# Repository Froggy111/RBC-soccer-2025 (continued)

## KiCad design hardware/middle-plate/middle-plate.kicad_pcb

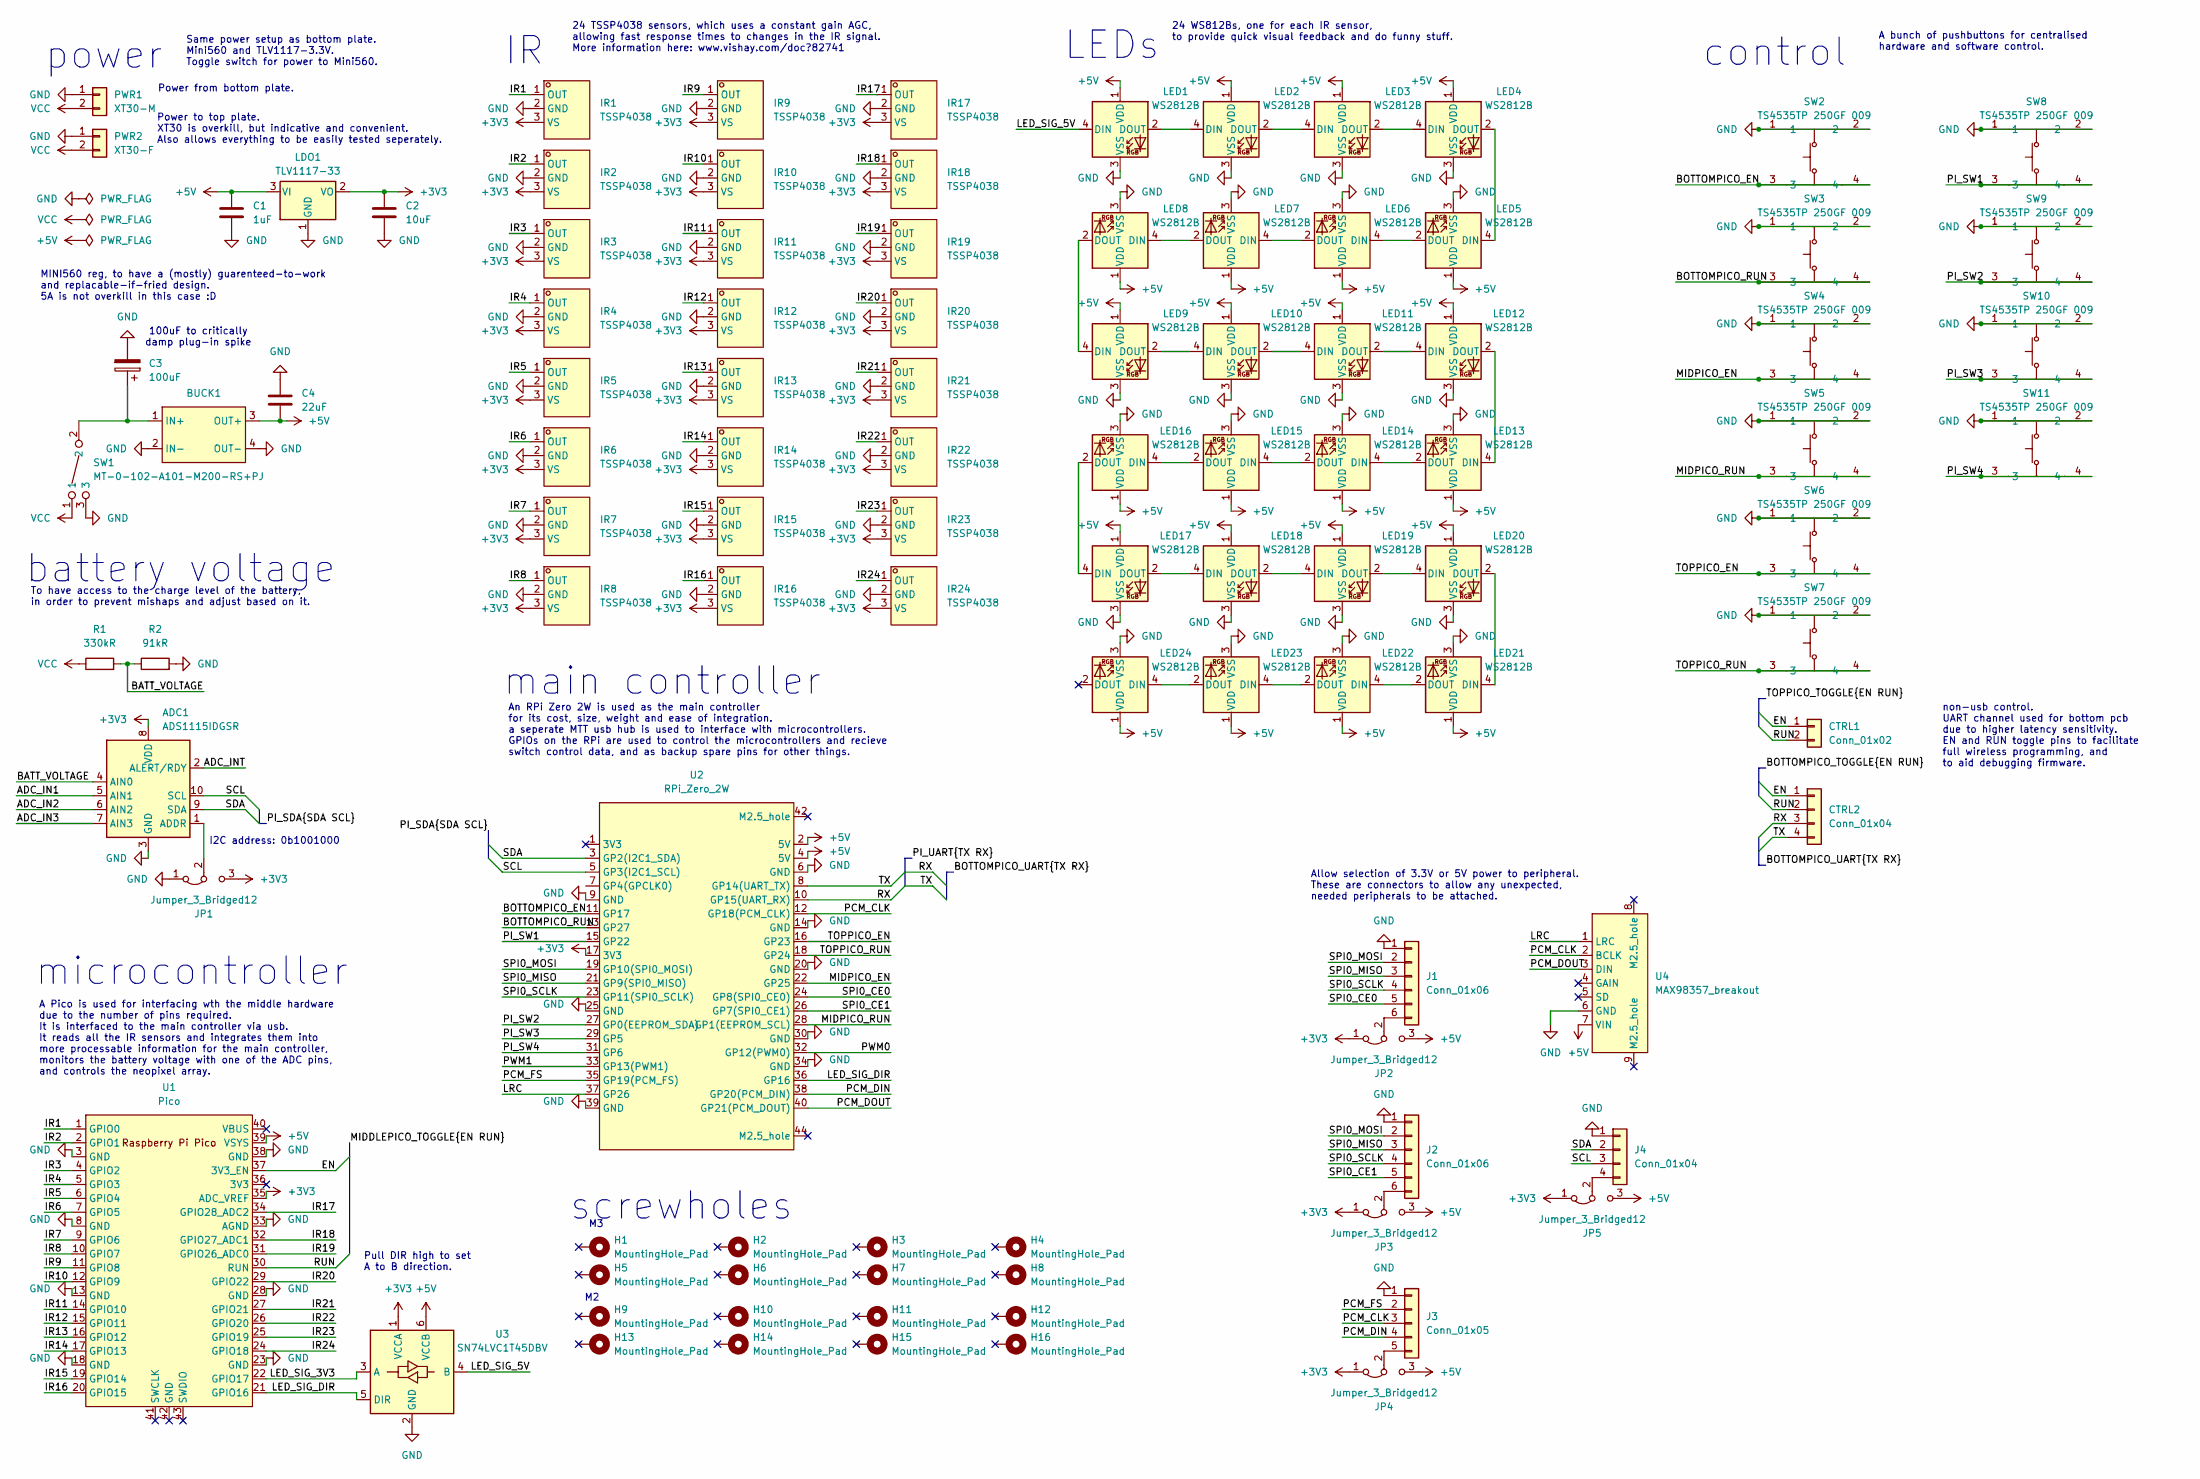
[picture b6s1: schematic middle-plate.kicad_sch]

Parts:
ADC1: ADS1115IDGSR; TSSOP-10_3x3mm_P0.5mm
BUCK1: mini560
C1: 1uF; C_0805_2012Metric_Pad1.15x1.40mm_HandSolder
C2: 10uF; C_0805_2012Metric_Pad1.15x1.40mm_HandSolder
C3: 100uF; CP_Elec_6.3x7.7
C4: 22uF; C_0805_2012Metric_Pad1.15x1.40mm_HandSolder
CTRL1: Conn_01x02; JST_XH_B2B-XH-A_1x02_P2.50mm_Vertical
CTRL2: Conn_01x04; JST_XH_B4B-XH-A_1x04_P2.50mm_Vertical
H1, H2, H3, H4, H5, H6, H7, H8: MountingHole_Pad; MountingHole_3.2mm_M3_Pad_Via
H9, H10, H11, H12, H13, H14, H15, H16: MountingHole_Pad; MountingHole_2.2mm_M2_Pad_Via
IR1, IR2, IR3, IR4, IR5, IR6, IR7, IR8, IR9, IR10, IR11, IR12, IR13, IR14, IR15, IR16, IR17, IR18, IR19, IR20, IR21, IR22, IR23, IR24: TSSP4038; SENSOR-TH_TSSP40X; LCSC Part C143753
J1, J2: Conn_01x06; JST_XH_B6B-XH-A_1x06_P2.50mm_Vertical
J3: Conn_01x05; JST_XH_B5B-XH-A_1x05_P2.50mm_Vertical
J4: Conn_01x04; JST_XH_B4B-XH-A_1x04_P2.50mm_Vertical
JP1: Jumper_3_Bridged12; PinHeader_1x03_P1.27mm_Vertical
JP2, JP3, JP4, JP5: Jumper_3_Bridged12; PinHeader_1x03_P2.54mm_Vertical
LDO1: TLV1117-33; SOT-223-3_TabPin2
LED1, LED2, LED3, LED4, LED5, LED6, LED7, LED8, LED9, LED10, LED11, LED12, LED13, LED14, LED15, LED16, LED17, LED18, LED19, LED20, LED21, LED22, LED23, LED24: WS2812B; LED_WS2812B-Mini_PLCC4_3.5x3.5mm
PWR1: XT30-M; AMASS_XT30U-M_1x02_P5.0mm_Vertical
PWR2: XT30-F; AMASS_XT30U-F_1x02_P5.0mm_Vertical
R1: 330kR; R_1206_3216Metric_Pad1.30x1.75mm_HandSolder
R2: 91kR; R_1206_3216Metric_Pad1.30x1.75mm_HandSolder
SW1: MT-0-102-A101-M200-RS+PJ; SW-TH_MT-0-103-A101-M200-RS; LCSC Part C1788492
SW2, SW3, SW4, SW5, SW6, SW7, SW8, SW9, SW10, SW11: TS4535TP 250GF 009; SW-SMD_4P-L4.5-W4.5-P3.00-LS6.8; LCSC Part C5342982
U1: Pico; RPi_Pico_SMD_TH_USBC_cable_cutout
U2: RPi_Zero_2W; RPi_Zero_2W_no_front_mountingholes
U3: SN74LVC1T45DBV; SOT-23-6
U4: MAX98357_breakout

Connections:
+3V3: ADC1.8 (VDD), C2.2, IR1.3 (VS), IR2.3 (VS), IR3.3 (VS), IR4.3 (VS), IR5.3 (VS), IR6.3 (VS), IR7.3 (VS), IR8.3 (VS), IR9.3 (VS), IR10.3 (VS), IR11.3 (VS), IR12.3 (VS), IR13.3 (VS), IR14.3 (VS), IR15.3 (VS), IR16.3 (VS), IR17.3 (VS), IR18.3 (VS), IR19.3 (VS), IR20.3 (VS), IR21.3 (VS), IR22.3 (VS), IR23.3 (VS), IR24.3 (VS), JP1.3 (B), JP2.1 (A), JP3.1 (A), JP4.1 (A), JP5.1 (A), LDO1.2 (VO), U1.35 (ADC_VREF), U2.17 (3V3), U3.1 (VCCA)
+5V: BUCK1.3 (OUT+), C1.2, C4.2, JP2.3 (B), JP3.3 (B), JP4.3 (B), JP5.3 (B), LDO1.3 (VI), LED1.1 (VDD), LED2.1 (VDD), LED3.1 (VDD), LED4.1 (VDD), LED5.1 (VDD), LED6.1 (VDD), LED7.1 (VDD), LED8.1 (VDD), LED9.1 (VDD), LED10.1 (VDD), LED11.1 (VDD), LED12.1 (VDD), LED13.1 (VDD), LED14.1 (VDD), LED15.1 (VDD), LED16.1 (VDD), LED17.1 (VDD), LED18.1 (VDD), LED19.1 (VDD), LED20.1 (VDD), LED21.1 (VDD), LED22.1 (VDD), LED23.1 (VDD), LED24.1 (VDD), U1.39 (VSYS), U2.2 (5V), U2.4 (5V), U3.6 (VCCB), U4.7 (VIN)
/ADC_IN1: ADC1.5 (AIN1)
/ADC_IN2: ADC1.6 (AIN2)
/ADC_IN3: ADC1.7 (AIN3)
/ADC_INT: ADC1.2 (ALERT/RDY)
/BATT_VOLTAGE: ADC1.4 (AIN0), R1.2, R2.1
/BOTTOMPICO_EN: SW2.3, SW2.4, U2.11 (GP17)
/BOTTOMPICO_RUN: SW3.3, SW3.4, U2.13 (GP27)
/EN: CTRL1.1, CTRL2.1, U1.37 (3V3_EN)
/IR1: IR1.1 (OUT), U1.1 (GPIO0)
/IR2: IR2.1 (OUT), U1.2 (GPIO1)
/IR3: IR3.1 (OUT), U1.4 (GPIO2)
/IR4: IR4.1 (OUT), U1.5 (GPIO3)
/IR5: IR5.1 (OUT), U1.6 (GPIO4)
/IR6: IR6.1 (OUT), U1.7 (GPIO5)
/IR7: IR7.1 (OUT), U1.9 (GPIO6)
/IR8: IR8.1 (OUT), U1.10 (GPIO7)
/IR9: IR9.1 (OUT), U1.11 (GPIO8)
/IR10: IR10.1 (OUT), U1.12 (GPIO9)
/IR11: IR11.1 (OUT), U1.14 (GPIO10)
/IR12: IR12.1 (OUT), U1.15 (GPIO11)
/IR13: IR13.1 (OUT), U1.16 (GPIO12)
/IR14: IR14.1 (OUT), U1.17 (GPIO13)
/IR15: IR15.1 (OUT), U1.19 (GPIO14)
/IR16: IR16.1 (OUT), U1.20 (GPIO15)
/IR17: IR17.1 (OUT), U1.34 (GPIO28_ADC2)
/IR18: IR18.1 (OUT), U1.32 (GPIO27_ADC1)
/IR19: IR19.1 (OUT), U1.31 (GPIO26_ADC0)
/IR20: IR20.1 (OUT), U1.29 (GPIO22)
/IR21: IR21.1 (OUT), U1.27 (GPIO21)
/IR22: IR22.1 (OUT), U1.26 (GPIO20)
/IR23: IR23.1 (OUT), U1.25 (GPIO19)
/IR24: IR24.1 (OUT), U1.24 (GPIO18)
/LED_SIG_3V3: U1.22 (GPIO17), U3.3 (A)
/LED_SIG_5V: LED1.4 (DIN), U3.4 (B)
/LED_SIG_DIR: U1.21 (GPIO16), U2.36 (GP16), U3.5 (DIR)
/LRC: U2.37 (GP26), U4.1 (LRC)
/MIDPICO_EN: SW4.3, SW4.4, U2.22 (GP25)
/MIDPICO_RUN: SW5.3, SW5.4, U2.28 (GP1(EEPROM_SCL))
/PCM_CLK: J3.3, U2.12 (GP18(PCM_CLK)), U4.2 (BCLK)
/PCM_DIN: J3.4, U2.38 (GP20(PCM_DIN))
/PCM_DOUT: U2.40 (GP21(PCM_DOUT)), U4.3 (DIN)
/PCM_FS: J3.2, U2.35 (GP19(PCM_FS))
/PI_SW1: SW8.3, SW8.4, U2.15 (GP22)
/PI_SW2: SW9.3, SW9.4, U2.27 (GP0(EEPROM_SDA))
/PI_SW3: SW10.3, SW10.4, U2.29 (GP5)
/PI_SW4: SW11.3, SW11.4, U2.31 (GP6)
/PWM0: U2.32 (GP12(PWM0))
/PWM1: U2.33 (GP13(PWM1))
/RUN: CTRL1.2, CTRL2.2, U1.30 (RUN)
/RX: CTRL2.3, U2.10 (GP15(UART_RX))
/SCL: ADC1.10 (SCL), J4.3, U2.5 (GP3(I2C1_SCL))
/SDA: ADC1.9 (SDA), J4.2, U2.3 (GP2(I2C1_SDA))
/SPI0_CE0: J1.5, U2.24 (GP8(SPI0_CE0))
/SPI0_CE1: J2.5, U2.26 (GP7(SPI0_CE1))
/SPI0_MISO: J1.3, J2.3, U2.21 (GP9(SPI0_MISO))
/SPI0_MOSI: J1.2, J2.2, U2.19 (GP10(SPI0_MOSI))
/SPI0_SCLK: J1.4, J2.4, U2.23 (GP11(SPI0_SCLK))
/TOPPICO_EN: SW6.3, SW6.4, U2.16 (GP23)
/TOPPICO_RUN: SW7.3, SW7.4, U2.18 (GP24)
/TX: CTRL2.4, U2.8 (GP14(UART_TX))
GND: ADC1.3 (GND), BUCK1.2 (IN-), BUCK1.4 (OUT-), C1.1, C2.1, C3.2, C4.1, IR1.2 (GND), IR2.2 (GND), IR3.2 (GND), IR4.2 (GND), IR5.2 (GND), IR6.2 (GND), IR7.2 (GND), IR8.2 (GND), IR9.2 (GND), IR10.2 (GND), IR11.2 (GND), IR12.2 (GND), IR13.2 (GND), IR14.2 (GND), IR15.2 (GND), IR16.2 (GND), IR17.2 (GND), IR18.2 (GND), IR19.2 (GND), IR20.2 (GND), IR21.2 (GND), IR22.2 (GND), IR23.2 (GND), IR24.2 (GND), J1.1, J2.1, J3.1, J4.1, JP1.1 (A), LDO1.1 (GND), LED1.3 (VSS), LED2.3 (VSS), LED3.3 (VSS), LED4.3 (VSS), LED5.3 (VSS), LED6.3 (VSS), LED7.3 (VSS), LED8.3 (VSS), LED9.3 (VSS), LED10.3 (VSS), LED11.3 (VSS), LED12.3 (VSS), LED13.3 (VSS), LED14.3 (VSS), LED15.3 (VSS), LED16.3 (VSS), LED17.3 (VSS), LED18.3 (VSS), LED19.3 (VSS), LED20.3 (VSS), LED21.3 (VSS), LED22.3 (VSS), LED23.3 (VSS), LED24.3 (VSS), PWR1.1, PWR2.1, R2.2, SW1.3, SW2.1, SW2.2, SW3.1, SW3.2, SW4.1, SW4.2, SW5.1, SW5.2, SW6.1, SW6.2, SW7.1, SW7.2, SW8.1, SW8.2, SW9.1, SW9.2, SW10.1, SW10.2, SW11.1, SW11.2, U1.3 (GND), U1.8 (GND), U1.13 (GND), U1.18 (GND), U1.23 (GND), U1.28 (GND), U1.33 (AGND), U1.38 (GND), U2.6 (GND), U2.9 (GND), U2.14 (GND), U2.20 (GND), U2.25 (GND), U2.30 (GND), U2.34 (GND), U2.39 (GND), U3.2 (GND), U4.6 (GND)
unnamed: ADC1.1 (ADDR), JP1.2 (C)
unnamed: BUCK1.1 (IN+), C3.1, SW1.2
unnamed: J1.6, JP2.2 (C)
unnamed: J2.6, JP3.2 (C)
unnamed: J3.5, JP4.2 (C)
unnamed: J4.4, JP5.2 (C)
unnamed: LED1.2 (DOUT), LED2.4 (DIN)
unnamed: LED2.2 (DOUT), LED3.4 (DIN)
unnamed: LED3.2 (DOUT), LED4.4 (DIN)
unnamed: LED4.2 (DOUT), LED5.4 (DIN)
unnamed: LED5.2 (DOUT), LED6.4 (DIN)
unnamed: LED6.2 (DOUT), LED7.4 (DIN)
unnamed: LED7.2 (DOUT), LED8.4 (DIN)
unnamed: LED8.2 (DOUT), LED9.4 (DIN)
unnamed: LED9.2 (DOUT), LED10.4 (DIN)
unnamed: LED10.2 (DOUT), LED11.4 (DIN)
unnamed: LED11.2 (DOUT), LED12.4 (DIN)
unnamed: LED12.2 (DOUT), LED13.4 (DIN)
unnamed: LED13.2 (DOUT), LED14.4 (DIN)
unnamed: LED14.2 (DOUT), LED15.4 (DIN)
unnamed: LED15.2 (DOUT), LED16.4 (DIN)
unnamed: LED16.2 (DOUT), LED17.4 (DIN)
unnamed: LED17.2 (DOUT), LED18.4 (DIN)
unnamed: LED18.2 (DOUT), LED19.4 (DIN)
unnamed: LED19.2 (DOUT), LED20.4 (DIN)
unnamed: LED20.2 (DOUT), LED21.4 (DIN)
unnamed: LED21.2 (DOUT), LED22.4 (DIN)
unnamed: LED22.2 (DOUT), LED23.4 (DIN)
unnamed: LED23.2 (DOUT), LED24.4 (DIN)
VCC: PWR1.2, PWR2.2, R1.1, SW1.1

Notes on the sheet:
screwholes
Allow selection of 3.3V or 5V power to peripheral. These are connectors to allow any unexpected, needed peripherals to be attached.
microcontroller
24 WS812Bs, one for each IR sensor, to provide quick visual feedback and do funny stuff.
main controller
24 TSSP4038 sensors, which uses a constant gain AGC, allowing fast response times to changes in the IR signal. More information here: www.vishay.com/doc?82741
power
MINI560 reg, to have a (mostly) guarenteed-to-work and replacable-if-fried design. 5A is not overkill in this case :D
control
I2C address: 0b1001000
Pull DIR high to set A to B direction.
LEDs
Power from bottom plate.
A bunch of pushbuttons for centralised hardware and software control.
A Pico is used for interfacing wth the middle hardware due to the number of pins required. It is interfaced to the main controller via usb. It reads all the IR sensors and integrates them into more processable information for the main controller, monitors the battery voltage with one of the ADC pin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
An RPi Zero 2W is used as the main controller for its cost, size, weight and ease of integration. a seperate MTT usb hub is used to interface with microcontrollers. GPIOs on the RPi are used to control the microcontrollers and recieve switch control data, and as backup spare pins for other things.
To have access to the charge level of the battery, in order to prevent mishaps and adjust based on it.
Power to top plate. XT30 is overkill, but indicative and convenient. Also allows everything to be easily tested seperately.
100uF to critically damp plug-in spike
battery voltage
Same power setup as bottom plate. Mini560 and TLV1117-3.3V. Toggle switch for power to Mini560.
non-usb control. UART channel used for bottom pcb due to higher latency sensitivity. EN and RUN toggle pins to facilitate full wireless programming, and to aid debugging firmware.

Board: 2 copper layers, 101 parts (12 on the bottom side), 87 nets, no tracks yet.

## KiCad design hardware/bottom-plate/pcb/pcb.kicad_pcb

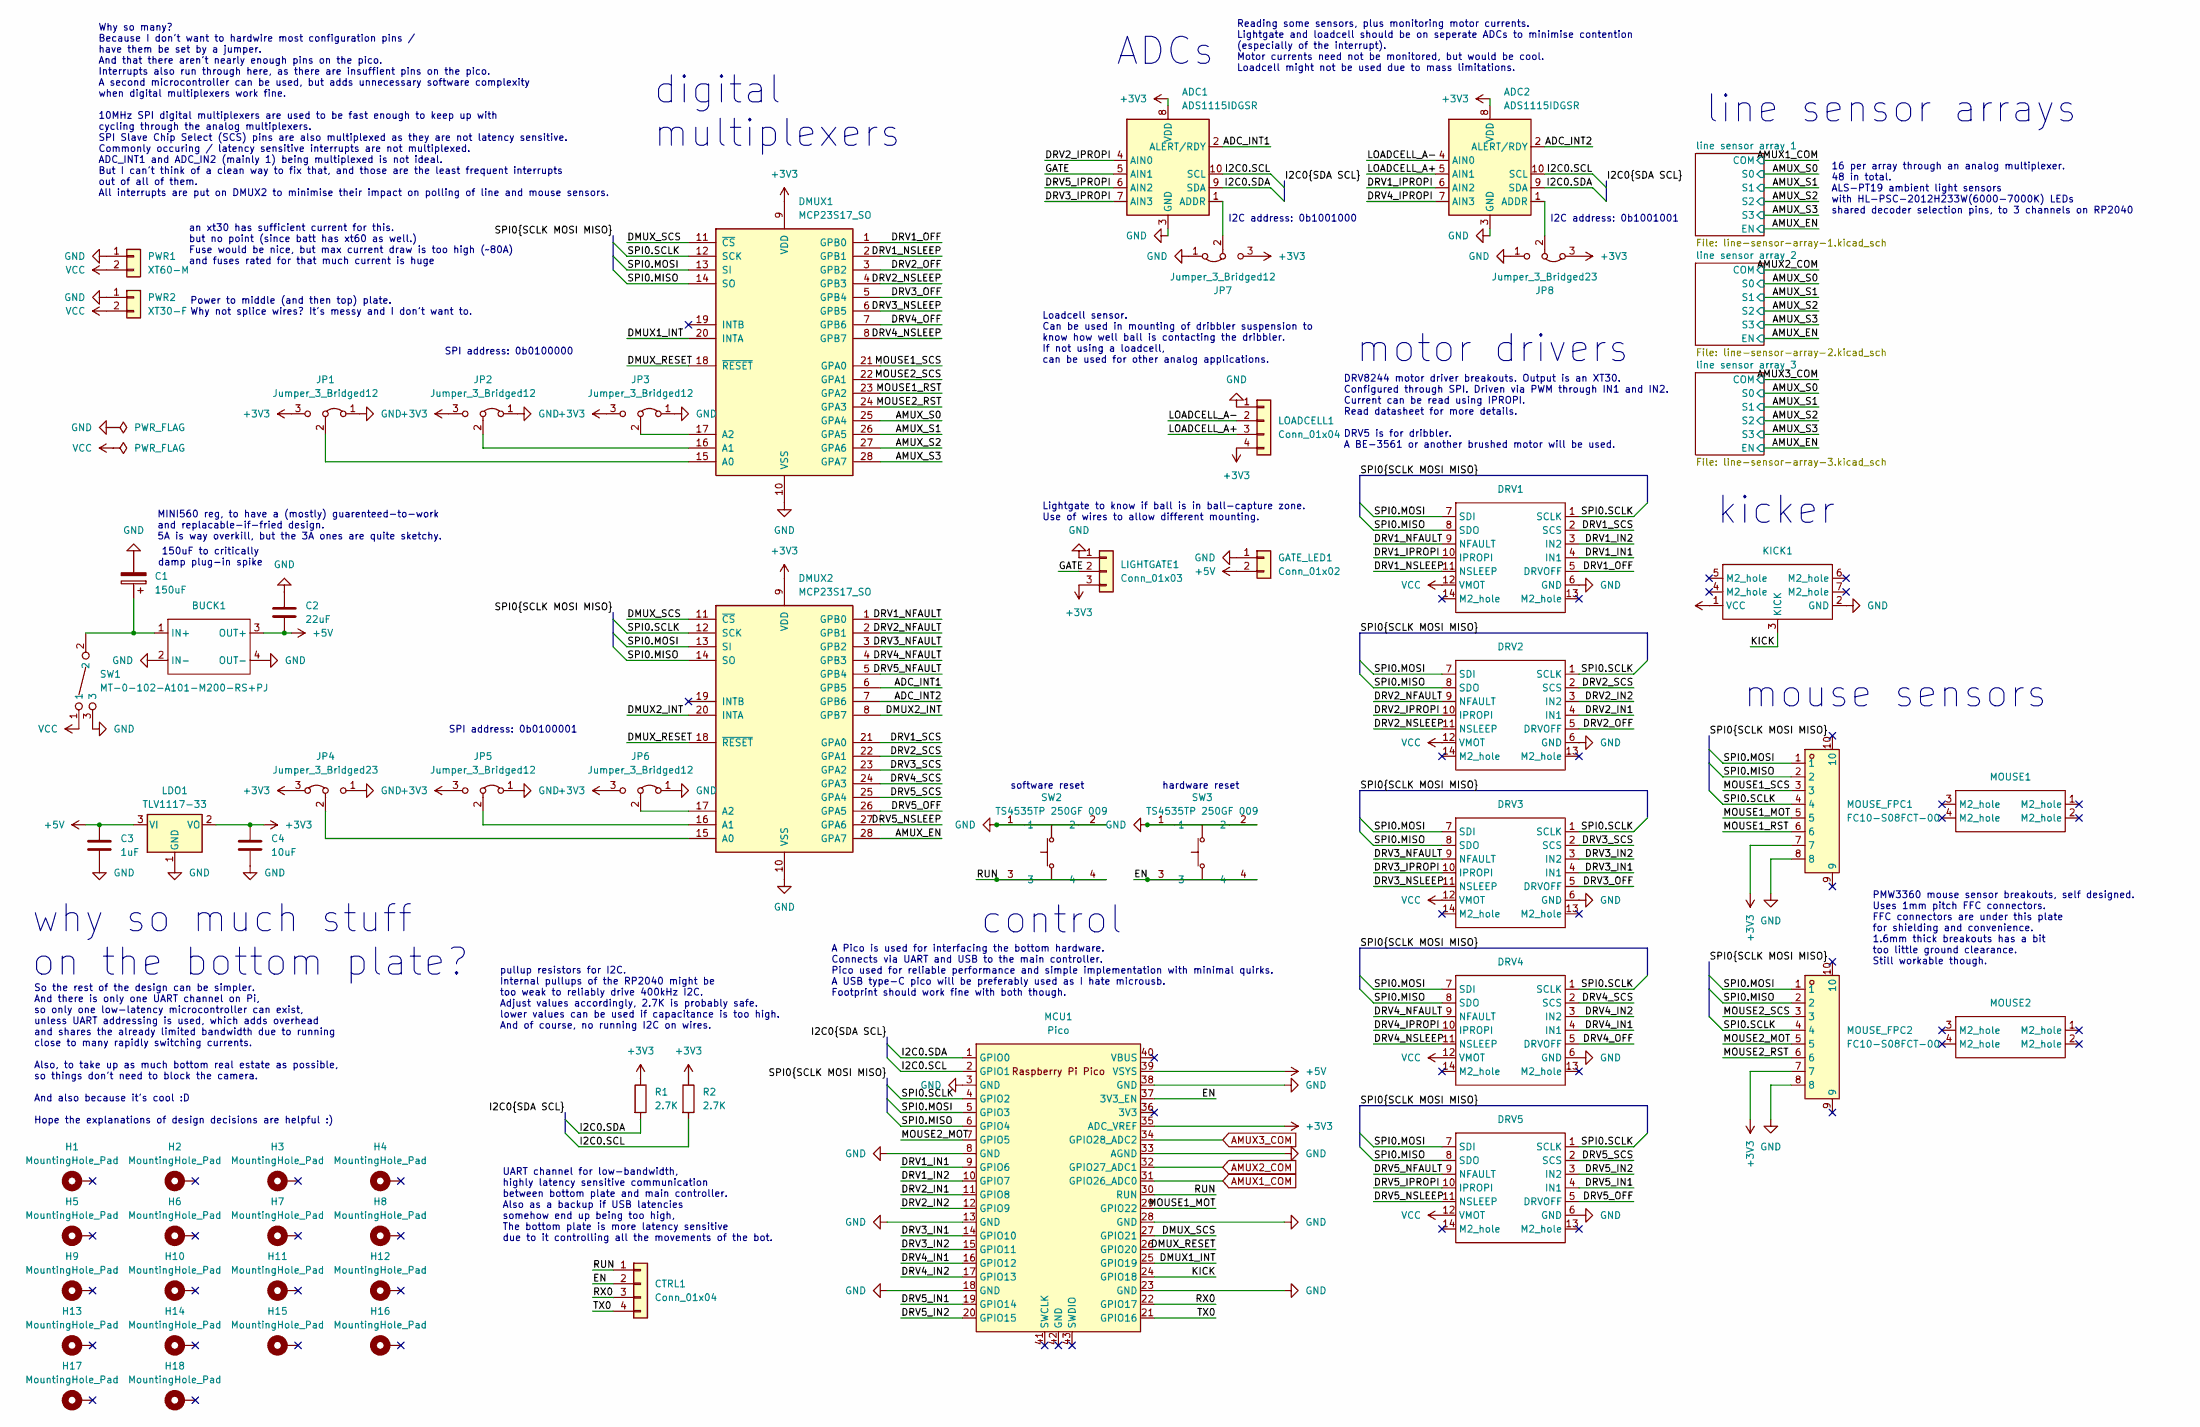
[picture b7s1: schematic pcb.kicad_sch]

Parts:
ADC1, ADC2: ADS1115IDGSR; TSSOP-10_3x3mm_P0.5mm
BUCK1: mini560
C1: 150uF; CP_Elec_6.3x7.7
C2: 22uF; C_0805_2012Metric_Pad1.15x1.40mm_HandSolder
C3: 1uF; C_0805_2012Metric_Pad1.15x1.40mm_HandSolder
C4: 10uF; C_0805_2012Metric_Pad1.15x1.40mm_HandSolder
CTRL1: Conn_01x04; JST_XH_B4B-XH-A_1x04_P2.50mm_Vertical
DMUX1, DMUX2: MCP23S17_SO; SOIC-28W_7.5x17.9mm_P1.27mm
DRV1, DRV2, DRV3, DRV4, DRV5: DRV8224_breakout
GATE_LED1: Conn_01x02; JST_XH_B2B-XH-A_1x02_P2.50mm_Vertical
H1, H2, H3, H4, H5, H6, H7, H8: MountingHole_Pad; MountingHole_3.2mm_M3_Pad_Via
H9, H10, H11, H12, H13, H14, H15, H16, H17, H18: MountingHole_Pad; MountingHole_2.2mm_M2_Pad_Via
JP1, JP2, JP3, JP5, JP6, JP7: Jumper_3_Bridged12; PinHeader_1x03_P1.27mm_Vertical
JP4, JP8: Jumper_3_Bridged23; PinHeader_1x03_P1.27mm_Vertical
KICK1: kicker
LDO1: TLV1117-33; SOT-223-3_TabPin2
LIGHTGATE1: Conn_01x03; JST_XH_B3B-XH-A_1x03_P2.50mm_Vertical
LOADCELL1: Conn_01x04; JST_XH_B4B-XH-A_1x04_P2.50mm_Vertical
MCU1: Pico; RPi_Pico_SMD_TH_USBC_cable_cutout
MOUSE1, MOUSE2: PMW3360_breakout
MOUSE_FPC1, MOUSE_FPC2: FC10-S08FCT-00; FPC-SMD_8P-P1.00_DEALON_FC10-S08FCT-00; LCSC Part C2998898
PWR1: XT60-M; AMASS_XT60-M_1x02_P7.20mm_Vertical
PWR2: XT30-F; AMASS_XT30U-F_1x02_P5.0mm_Vertical
R1, R2: 2.7K; R_0805_2012Metric_Pad1.15x1.40mm_HandSolder
SW1: MT-0-102-A101-M200-RS+PJ; SW-TH_MT-0-103-A101-M200-RS; LCSC Part C1788492
SW2, SW3: TS4535TP 250GF 009; SW-SMD_4P-L4.5-W4.5-P3.00-LS6.8; LCSC Part C5342982

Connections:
+3V3: ADC1.8 (VDD), ADC2.8 (VDD), C4.2, DMUX1.9 (VDD), DMUX2.9 (VDD), JP1.3 (B), JP2.3 (B), JP3.3 (B), JP4.3 (B), JP5.3 (B), JP6.3 (B), JP7.3 (B), JP8.3 (B), LDO1.2 (VO), LIGHTGATE1.3, LOADCELL1.4, MCU1.35 (ADC_VREF), MOUSE_FPC1.7, MOUSE_FPC2.7, R1.1, R2.1; also elsewhere on the board
+5V: BUCK1.3 (OUT+), C2.2, C3.2, GATE_LED1.2, LDO1.3 (VI), MCU1.39 (VSYS); also elsewhere on the board
/ADC_INT1: ADC1.2 (ALERT/RDY), DMUX2.6 (GPB5)
/ADC_INT2: ADC2.2 (ALERT/RDY), DMUX2.7 (GPB6)
/AMUX_EN: DMUX2.28 (GPA7); also elsewhere on the board
/AMUX_S0: DMUX1.25 (GPA4); also elsewhere on the board
/AMUX_S1: DMUX1.26 (GPA5); also elsewhere on the board
/AMUX_S2: DMUX1.27 (GPA6); also elsewhere on the board
/AMUX_S3: DMUX1.28 (GPA7); also elsewhere on the board
/DMUX1_INT: DMUX1.20 (INTA), MCU1.25 (GPIO19)
/DMUX2_INT: DMUX2.8 (GPB7), DMUX2.20 (INTA)
/DMUX_RESET: DMUX1.18 (~RESET), DMUX2.18 (~RESET), MCU1.26 (GPIO20)
/DMUX_SCS: DMUX1.11 (~CS), DMUX2.11 (~CS), MCU1.27 (GPIO21)
/DRV1_IN1: DRV1.4 (IN1), MCU1.9 (GPIO6)
/DRV1_IN2: DRV1.3 (IN2), MCU1.10 (GPIO7)
/DRV1_IPROPI: ADC2.6 (AIN2), DRV1.10 (IPROPI)
/DRV1_NFAULT: DMUX2.1 (GPB0), DRV1.9 (NFAULT)
/DRV1_NSLEEP: DMUX1.2 (GPB1), DRV1.11 (NSLEEP)
/DRV1_OFF: DMUX1.1 (GPB0), DRV1.5 (DRVOFF)
/DRV1_SCS: DMUX2.21 (GPA0), DRV1.2 (SCS)
/DRV2_IN1: DRV2.4 (IN1), MCU1.11 (GPIO8)
/DRV2_IN2: DRV2.3 (IN2), MCU1.12 (GPIO9)
/DRV2_IPROPI: ADC1.4 (AIN0), DRV2.10 (IPROPI)
/DRV2_NFAULT: DMUX2.2 (GPB1), DRV2.9 (NFAULT)
/DRV2_NSLEEP: DMUX1.4 (GPB3), DRV2.11 (NSLEEP)
/DRV2_OFF: DMUX1.3 (GPB2), DRV2.5 (DRVOFF)
/DRV2_SCS: DMUX2.22 (GPA1), DRV2.2 (SCS)
/DRV3_IN1: DRV3.4 (IN1), MCU1.14 (GPIO10)
/DRV3_IN2: DRV3.3 (IN2), MCU1.15 (GPIO11)
/DRV3_IPROPI: ADC1.7 (AIN3), DRV3.10 (IPROPI)
/DRV3_NFAULT: DMUX2.3 (GPB2), DRV3.9 (NFAULT)
/DRV3_NSLEEP: DMUX1.6 (GPB5), DRV3.11 (NSLEEP)
/DRV3_OFF: DMUX1.5 (GPB4), DRV3.5 (DRVOFF)
/DRV3_SCS: DMUX2.23 (GPA2), DRV3.2 (SCS)
/DRV4_IN1: DRV4.4 (IN1), MCU1.16 (GPIO12)
/DRV4_IN2: DRV4.3 (IN2), MCU1.17 (GPIO13)
/DRV4_IPROPI: ADC2.7 (AIN3), DRV4.10 (IPROPI)
/DRV4_NFAULT: DMUX2.4 (GPB3), DRV4.9 (NFAULT)
/DRV4_NSLEEP: DMUX1.8 (GPB7), DRV4.11 (NSLEEP)
/DRV4_OFF: DMUX1.7 (GPB6), DRV4.5 (DRVOFF)
/DRV4_SCS: DMUX2.24 (GPA3), DRV4.2 (SCS)
/DRV5_IN1: DRV5.4 (IN1), MCU1.19 (GPIO14)
/DRV5_IN2: DRV5.3 (IN2), MCU1.20 (GPIO15)
/DRV5_IPROPI: ADC1.6 (AIN2), DRV5.10 (IPROPI)
/DRV5_NFAULT: DMUX2.5 (GPB4), DRV5.9 (NFAULT)
/DRV5_NSLEEP: DMUX2.27 (GPA6), DRV5.11 (NSLEEP)
/DRV5_OFF: DMUX2.26 (GPA5), DRV5.5 (DRVOFF)
/DRV5_SCS: DMUX2.25 (GPA4), DRV5.2 (SCS)
/EN: CTRL1.2, MCU1.37 (3V3_EN), SW3.3, SW3.4
/GATE: ADC1.5 (AIN1), LIGHTGATE1.2
/I2C0.SCL: ADC1.10 (SCL), ADC2.10 (SCL), MCU1.2 (GPIO1), R2.2
/I2C0.SDA: ADC1.9 (SDA), ADC2.9 (SDA), MCU1.1 (GPIO0), R1.2
/KICK: KICK1.3 (KICK), MCU1.24 (GPIO18)
/LOADCELL_A+: ADC2.5 (AIN1), LOADCELL1.3
/LOADCELL_A-: ADC2.4 (AIN0), LOADCELL1.2
/MOUSE1_MOT: MCU1.29 (GPIO22), MOUSE_FPC1.5
/MOUSE1_RST: DMUX1.23 (GPA2), MOUSE_FPC1.6
/MOUSE1_SCS: DMUX1.21 (GPA0), MOUSE_FPC1.3
/MOUSE2_MOT: MCU1.7 (GPIO5), MOUSE_FPC2.5
/MOUSE2_RST: DMUX1.24 (GPA3), MOUSE_FPC2.6
/MOUSE2_SCS: DMUX1.22 (GPA1), MOUSE_FPC2.3
/RUN: CTRL1.1, MCU1.30 (RUN), SW2.3, SW2.4
/RX0: CTRL1.3, MCU1.22 (GPIO17)
/SPI0.MISO: DMUX1.14 (SO), DMUX2.14 (SO), DRV1.8 (SDO), DRV2.8 (SDO), DRV3.8 (SDO), DRV4.8 (SDO), DRV5.8 (SDO), MCU1.6 (GPIO4), MOUSE_FPC1.2, MOUSE_FPC2.2
/SPI0.MOSI: DMUX1.13 (SI), DMUX2.13 (SI), DRV1.7 (SDI), DRV2.7 (SDI), DRV3.7 (SDI), DRV4.7 (SDI), DRV5.7 (SDI), MCU1.5 (GPIO3), MOUSE_FPC1.1, MOUSE_FPC2.1
/SPI0.SCLK: DMUX1.12 (SCK), DMUX2.12 (SCK), DRV1.1 (SCLK), DRV2.1 (SCLK), DRV3.1 (SCLK), DRV4.1 (SCLK), DRV5.1 (SCLK), MCU1.4 (GPIO2), MOUSE_FPC1.4, MOUSE_FPC2.4
/TX0: CTRL1.4, MCU1.21 (GPIO16)
AMUX1_COM: MCU1.31 (GPIO26_ADC0); also elsewhere on the board
AMUX2_COM: MCU1.32 (GPIO27_ADC1); also elsewhere on the board
AMUX3_COM: MCU1.34 (GPIO28_ADC2); also elsewhere on the board
GND: ADC1.3 (GND), ADC2.3 (GND), BUCK1.2 (IN-), BUCK1.4 (OUT-), C1.2, C2.1, C3.1, C4.1, DMUX1.10 (VSS), DMUX2.10 (VSS), DRV1.6 (GND), DRV2.6 (GND), DRV3.6 (GND), DRV4.6 (GND), DRV5.6 (GND), GATE_LED1.1, JP1.1 (A), JP2.1 (A), JP3.1 (A), JP4.1 (A), JP5.1 (A), JP6.1 (A), JP7.1 (A), JP8.1 (A), KICK1.2 (GND), LDO1.1 (GND), LIGHTGATE1.1, LOADCELL1.1, MCU1.3 (GND), MCU1.8 (GND), MCU1.13 (GND), MCU1.18 (GND), MCU1.23 (GND), MCU1.28 (GND), MCU1.33 (AGND), MCU1.38 (GND), MOUSE_FPC1.8, MOUSE_FPC2.8, PWR1.1, PWR2.1, SW1.3, SW2.1, SW2.2, SW3.1, SW3.2; also elsewhere on the board
unnamed: ADC1.1 (ADDR), JP7.2 (C)
unnamed: ADC2.1 (ADDR), JP8.2 (C)
unnamed: BUCK1.1 (IN+), C1.1, SW1.2
unnamed: DMUX1.15 (A0), JP1.2 (C)
unnamed: DMUX1.16 (A1), JP2.2 (C)
unnamed: DMUX1.17 (A2), JP3.2 (C)
unnamed: DMUX2.15 (A0), JP4.2 (C)
unnamed: DMUX2.16 (A1), JP5.2 (C)
unnamed: DMUX2.17 (A2), JP6.2 (C)
VCC: DRV1.12 (VMOT), DRV2.12 (VMOT), DRV3.12 (VMOT), DRV4.12 (VMOT), DRV5.12 (VMOT), KICK1.1 (VCC), PWR1.2, PWR2.2, SW1.1

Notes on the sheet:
line sensor arrays
Why so many? Because I don't want to hardwire most configuration pins / have them be set by a jumper. And that there aren't nearly enough pins on the pico. Interrupts also run through here, as there are insuffient pins on the pico. A second microcontroller can be used, but adds unnecessary software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
Lightgate to know if ball is in ball-capture zone. Use of wires to allow different mounting.
digital multiplexers
control
I2C address: 0b1001000
150uF to critically damp plug-in spike
Power to middle (and then top) plate. Why not splice wires? It's messy and I don't want to.
PMW3360 mouse sensor breakouts, self designed. Uses 1mm pitch FFC connectors. FFC connectors are under this plate for shielding and convenience. 1.6mm thick breakouts has a bit too little ground clearance. Still workable though.
MINI560 reg, to have a (mostly) guarenteed-to-work and replacable-if-fried design. 5A is way overkill, but the 3A ones are quite sketchy.
UART channel for low-bandwidth, highly latency sensitive communication between bottom plate and main controller. Also as a backup if USB latencies somehow end up being too high, The bottom plate is more latency sensitive due to it controlling all the movements of the bot.
A Pico is used for interfacing the bottom hardware. Connects via UART and USB to the main controller. Pico used for reliable performance and simple implementation with minimal quirks. A USB type-C pico will be preferably used as I hate microusb. Footprint should work fine with both though.
So the rest of the design can be simpler. And there is only one UART channel on Pi, so only one low-latency microcontroller can exist, unless UART addressing is used, which adds overhead and shares the already limited bandwidth due to running close to many rapidly switching currents. Also, to take 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
mouse sensors
SPI address: 0b0100001
hardware reset
ADCs
kicker
pullup resistors for I2C. Internal pullups of the RP2040 might be too weak to reliably drive 400kHz I2C. Adjust values accordingly, 2.7K is probably safe. lower values can be used if capacitance is too high. And of course, no running I2C on wires.
an xt30 has sufficient current for this. but no point (since batt has xt60 as well.) Fuse would be nice, but max current draw is too high (~80A) and fuses rated for that much current is huge
SPI address: 0b0100000
I2C address: 0b1001001
Loadcell sensor. Can be used in mounting of dribbler suspension to know how well ball is contacting the dribbler. If not using a loadcell, can be used for other analog applications.
software reset
16 per array through an analog multiplexer. 48 in total. ALS-PT19 ambient light sensors with HL-PSC-2012H233W(6000-7000K) LEDs shared decoder selection pins, to 3 channels on RP2040
DRV8244 motor driver breakouts. Output is an XT30. Configured through SPI. Driven via PWM through IN1 and IN2. Current can be read using IPROPI. Read datasheet for more details. DRV5 is for dribbler. A BE-3561 or another brushed motor will be used.
Reading some sensors, plus monitoring motor currents. Lightgate and loadcell should be on seperate ADCs to minimise contention (especially of the interrupt). Motor currents need not be monitored, but would be cool. Loadcell might not be used due to mass limitations.
why so much stuff on the bottom plate?
motor drivers

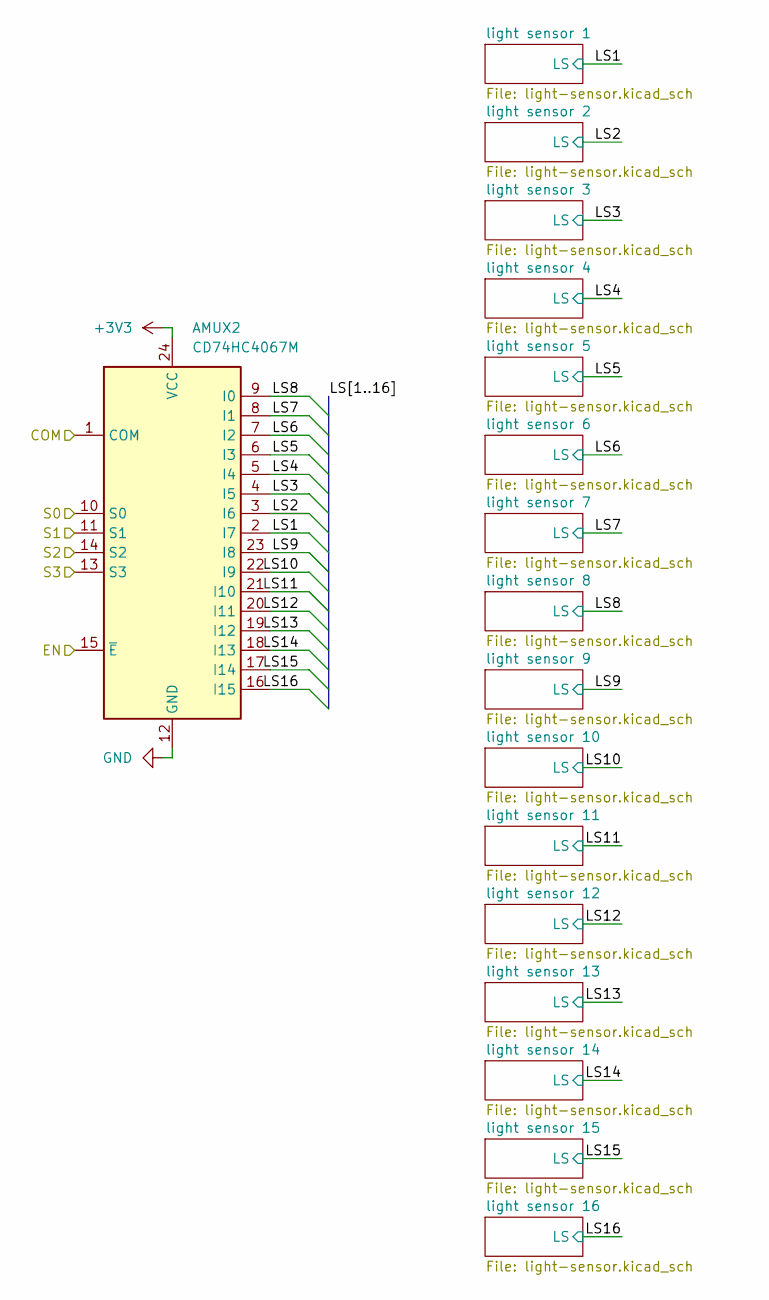
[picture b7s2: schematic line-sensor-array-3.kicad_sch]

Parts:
AMUX2: CD74HC4067M; SOIC-24W_7.5x15.4mm_P1.27mm

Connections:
+3V3: AMUX2.24 (VCC); also elsewhere on the board
/AMUX_EN: AMUX2.15 (~E); also elsewhere on the board
/AMUX_S0: AMUX2.10 (S0); also elsewhere on the board
/AMUX_S1: AMUX2.11 (S1); also elsewhere on the board
/AMUX_S2: AMUX2.14 (S2); also elsewhere on the board
/AMUX_S3: AMUX2.13 (S3); also elsewhere on the board
/line sensor array 2/LS1: AMUX2.2 (I7); also elsewhere on the board
/line sensor array 2/LS2: AMUX2.3 (I6); also elsewhere on the board
/line sensor array 2/LS3: AMUX2.4 (I5); also elsewhere on the board
/line sensor array 2/LS4: AMUX2.5 (I4); also elsewhere on the board
/line sensor array 2/LS5: AMUX2.6 (I3); also elsewhere on the board
/line sensor array 2/LS6: AMUX2.7 (I2); also elsewhere on the board
/line sensor array 2/LS7: AMUX2.8 (I1); also elsewhere on the board
/line sensor array 2/LS8: AMUX2.9 (I0); also elsewhere on the board
/line sensor array 2/LS9: AMUX2.23 (I8); also elsewhere on the board
/line sensor array 2/LS10: AMUX2.22 (I9); also elsewhere on the board
/line sensor array 2/LS11: AMUX2.21 (I10); also elsewhere on the board
/line sensor array 2/LS12: AMUX2.20 (I11); also elsewhere on the board
/line sensor array 2/LS13: AMUX2.19 (I12); also elsewhere on the board
/line sensor array 2/LS14: AMUX2.18 (I13); also elsewhere on the board
/line sensor array 2/LS15: AMUX2.17 (I14); also elsewhere on the board
/line sensor array 2/LS16: AMUX2.16 (I15); also elsewhere on the board
AMUX2_COM: AMUX2.1 (COM); also elsewhere on the board
GND: AMUX2.12 (GND); also elsewhere on the board

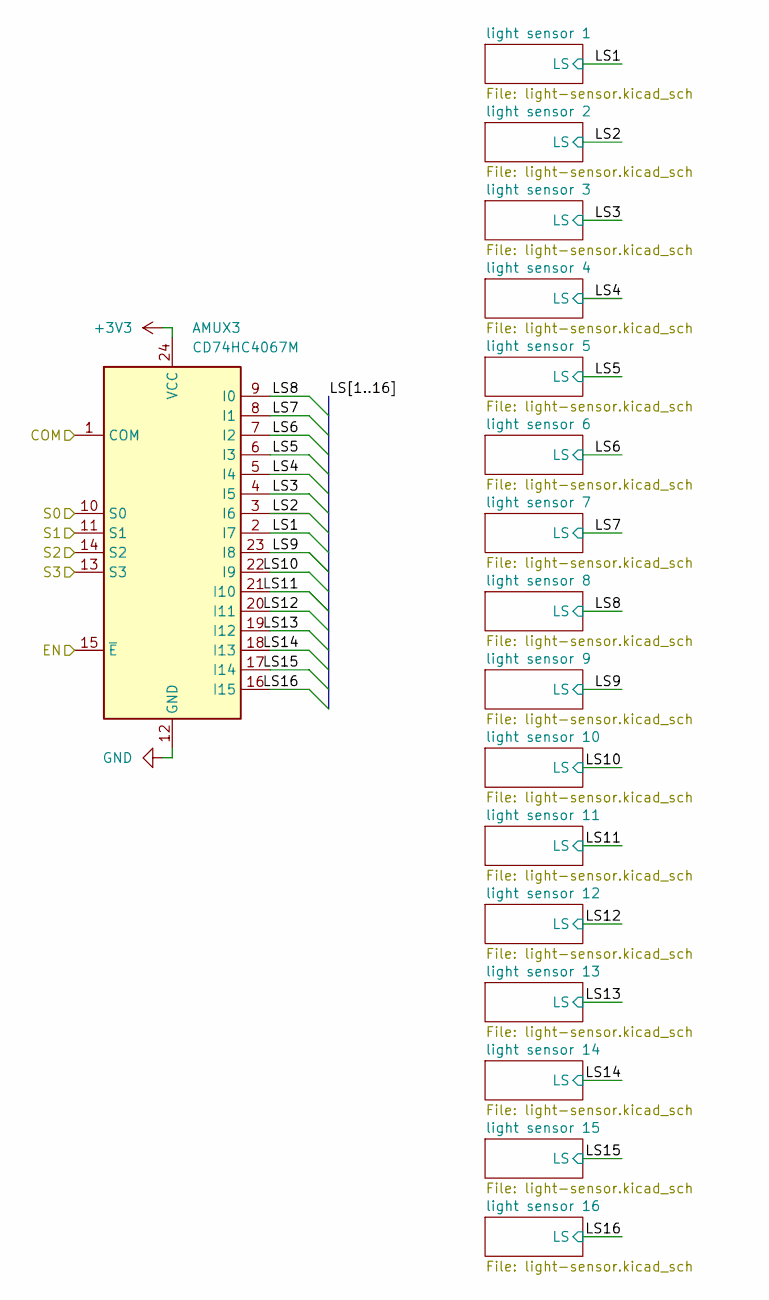
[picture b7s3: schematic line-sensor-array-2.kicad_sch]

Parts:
AMUX3: CD74HC4067M; SOIC-24W_7.5x15.4mm_P1.27mm

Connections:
+3V3: AMUX3.24 (VCC); also elsewhere on the board
/AMUX_EN: AMUX3.15 (~E); also elsewhere on the board
/AMUX_S0: AMUX3.10 (S0); also elsewhere on the board
/AMUX_S1: AMUX3.11 (S1); also elsewhere on the board
/AMUX_S2: AMUX3.14 (S2); also elsewhere on the board
/AMUX_S3: AMUX3.13 (S3); also elsewhere on the board
/line sensor array 3/LS1: AMUX3.2 (I7); also elsewhere on the board
/line sensor array 3/LS2: AMUX3.3 (I6); also elsewhere on the board
/line sensor array 3/LS3: AMUX3.4 (I5); also elsewhere on the board
/line sensor array 3/LS4: AMUX3.5 (I4); also elsewhere on the board
/line sensor array 3/LS5: AMUX3.6 (I3); also elsewhere on the board
/line sensor array 3/LS6: AMUX3.7 (I2); also elsewhere on the board
/line sensor array 3/LS7: AMUX3.8 (I1); also elsewhere on the board
/line sensor array 3/LS8: AMUX3.9 (I0); also elsewhere on the board
/line sensor array 3/LS9: AMUX3.23 (I8); also elsewhere on the board
/line sensor array 3/LS10: AMUX3.22 (I9); also elsewhere on the board
/line sensor array 3/LS11: AMUX3.21 (I10); also elsewhere on the board
/line sensor array 3/LS12: AMUX3.20 (I11); also elsewhere on the board
/line sensor array 3/LS13: AMUX3.19 (I12); also elsewhere on the board
/line sensor array 3/LS14: AMUX3.18 (I13); also elsewhere on the board
/line sensor array 3/LS15: AMUX3.17 (I14); also elsewhere on the board
/line sensor array 3/LS16: AMUX3.16 (I15); also elsewhere on the board
AMUX3_COM: AMUX3.1 (COM); also elsewhere on the board
GND: AMUX3.12 (GND); also elsewhere on the board

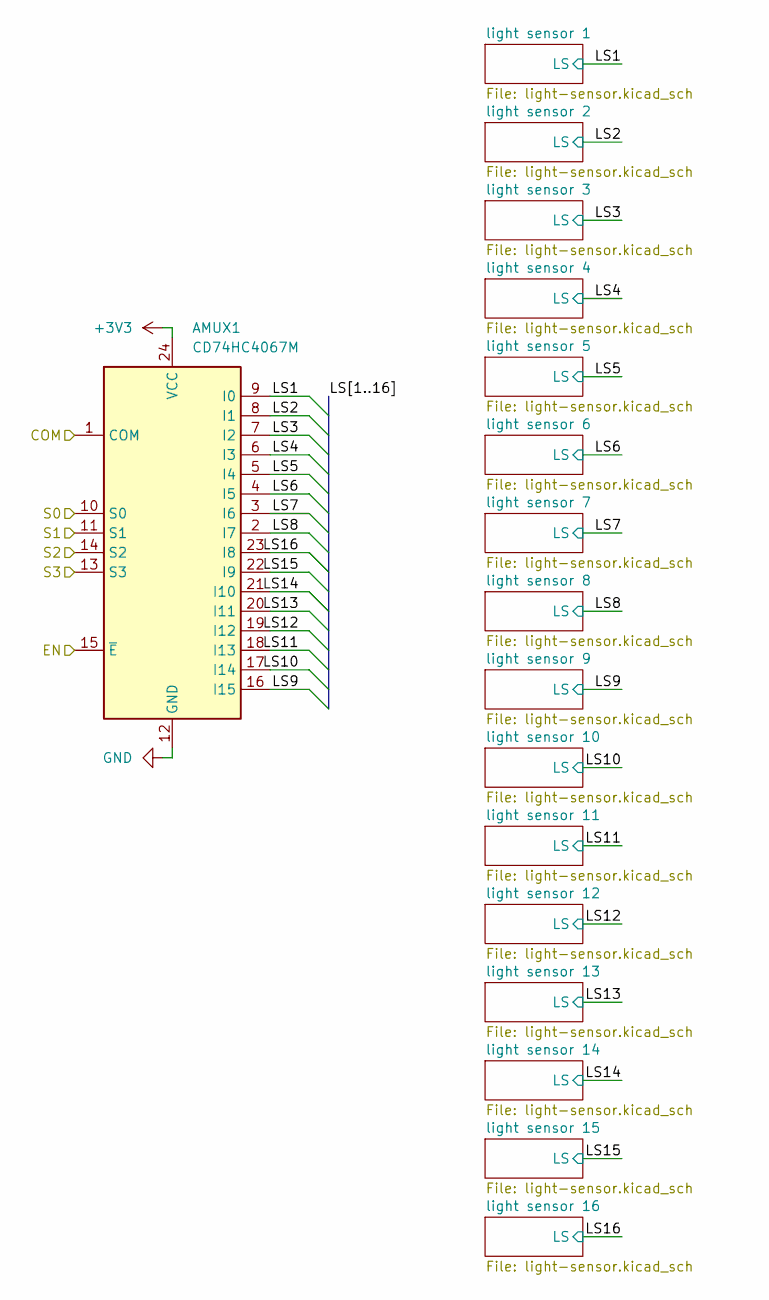
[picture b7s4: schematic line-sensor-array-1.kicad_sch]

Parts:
AMUX1: CD74HC4067M; SOIC-24W_7.5x15.4mm_P1.27mm

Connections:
+3V3: AMUX1.24 (VCC); also elsewhere on the board
/AMUX_EN: AMUX1.15 (~E); also elsewhere on the board
/AMUX_S0: AMUX1.10 (S0); also elsewhere on the board
/AMUX_S1: AMUX1.11 (S1); also elsewhere on the board
/AMUX_S2: AMUX1.14 (S2); also elsewhere on the board
/AMUX_S3: AMUX1.13 (S3); also elsewhere on the board
/line sensor array 1/LS1: AMUX1.2 (I7); also elsewhere on the board
/line sensor array 1/LS2: AMUX1.3 (I6); also elsewhere on the board
/line sensor array 1/LS3: AMUX1.4 (I5); also elsewhere on the board
/line sensor array 1/LS4: AMUX1.5 (I4); also elsewhere on the board
/line sensor array 1/LS5: AMUX1.6 (I3); also elsewhere on the board
/line sensor array 1/LS6: AMUX1.7 (I2); also elsewhere on the board
/line sensor array 1/LS7: AMUX1.8 (I1); also elsewhere on the board
/line sensor array 1/LS8: AMUX1.9 (I0); also elsewhere on the board
/line sensor array 1/LS9: AMUX1.23 (I8); also elsewhere on the board
/line sensor array 1/LS10: AMUX1.22 (I9); also elsewhere on the board
/line sensor array 1/LS11: AMUX1.21 (I10); also elsewhere on the board
/line sensor array 1/LS12: AMUX1.20 (I11); also elsewhere on the board
/line sensor array 1/LS13: AMUX1.19 (I12); also elsewhere on the board
/line sensor array 1/LS14: AMUX1.18 (I13); also elsewhere on the board
/line sensor array 1/LS15: AMUX1.17 (I14); also elsewhere on the board
/line sensor array 1/LS16: AMUX1.16 (I15); also elsewhere on the board
AMUX1_COM: AMUX1.1 (COM); also elsewhere on the board
GND: AMUX1.12 (GND); also elsewhere on the board
